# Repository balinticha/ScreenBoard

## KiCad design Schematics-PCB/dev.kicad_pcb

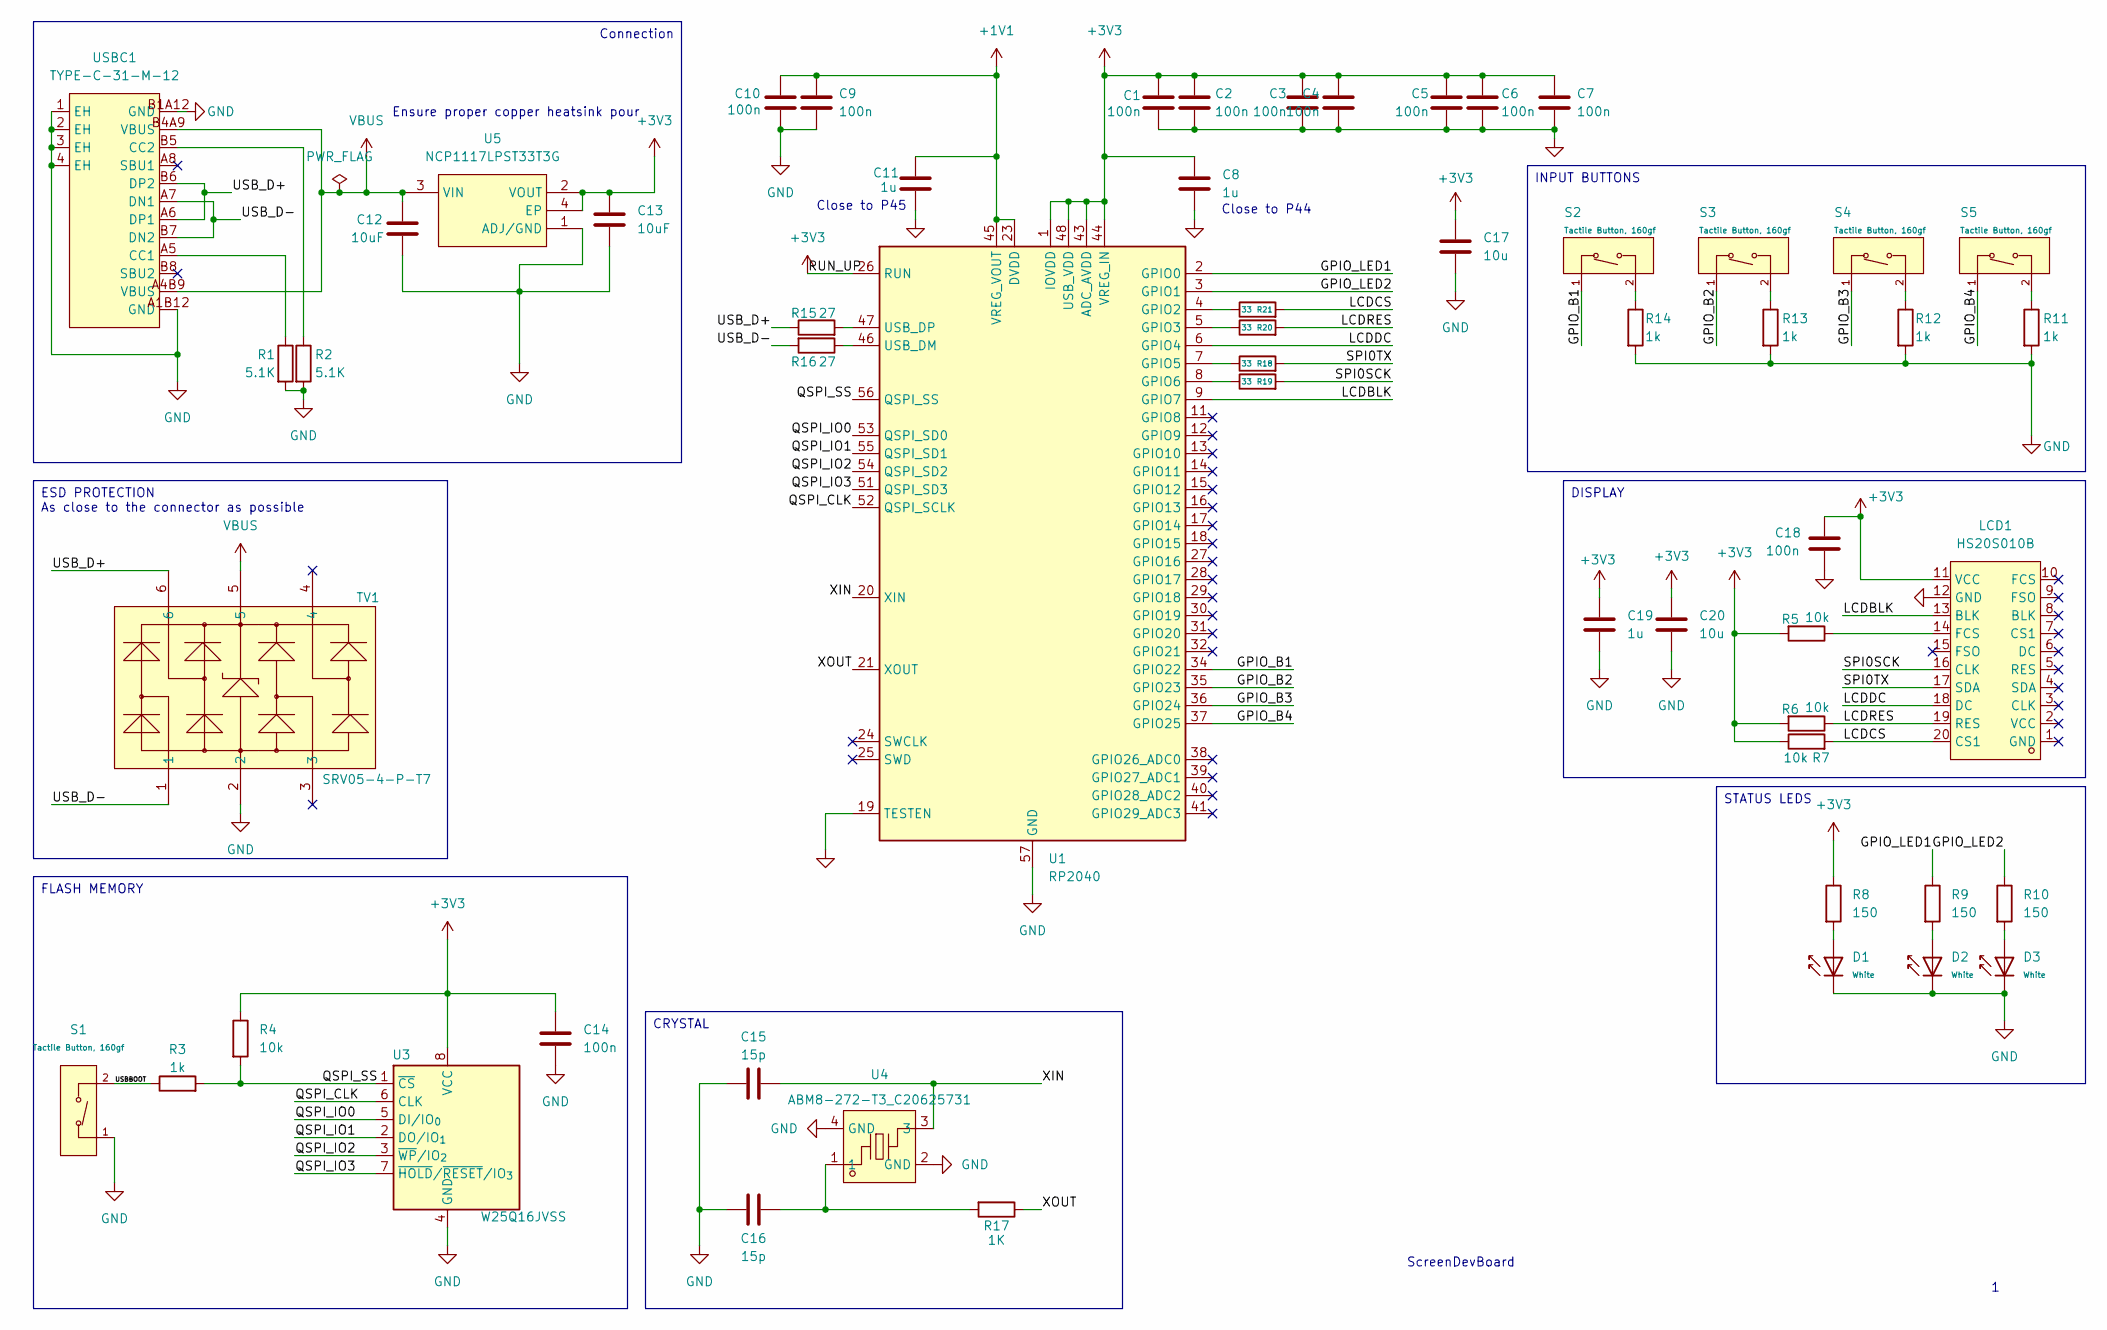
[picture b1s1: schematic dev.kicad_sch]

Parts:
C1, C2, C3, C4, C5, C6, C7, C9, C10: 100n; C_0402_1005Metric
C8, C11: 1u; C_0402_1005Metric
C12, C13: 10uF; C_0603_1608Metric
C14, C18: 100n; C_0603_1608Metric
C15, C16: 15p; C_0402_1005Metric
C17, C20: 10u; C_0603_1608Metric
C19: 1u; C_0603_1608Metric
D1, D2, D3: White; D_0805; Part KT-0805W; LCSC C34499
LCD1: HS20S010B; LCD-TH_HS20S010B; LCSC Part C5329586
R1, R2: 5.1K; R_0402_1005Metric
R3, R11, R12, R13, R14: 1k; R_0603_1608Metric
R4, R5, R6, R7: 10k; R_0603_1608Metric
R8, R9, R10: 150; R_0603_1608Metric
R15, R16: 27; R_0402_1005Metric
R17: 1K; R_0402_1005Metric
R18, R19, R20, R21: 33; R_0402_1005Metric
S1, S2, S3, S4, S5: Tactile Button, 160gf; SW_TS-1088-AR02016; Voltage Rating (Dc) 12V; Part TS-1088-AR02016; LCSC C720477
TV1: SRV05-4-P-T7; SOT-23-6_L2.9-W1.6-P0.95-LS2.8-BR; LCSC Part C85364
U1: RP2040; QFN-56-1EP_7x7mm_P0.4mm_EP3.2x3.2mm_ThermalVias; LCSC C2040
U3: W25Q16JVSS; SOIC-8_5.3x5.3mm_P1.27mm
U4: ABM8-272-T3_C20625731; CRYSTAL-SMD_4P-L3.2-W2.5-BL; LCSC Part C20625731
U5: NCP1117LPST33T3G; SOT-223_L6.5-W3.5-P2.30-LS7.0-BR; LCSC Part C146799
USBC1: TYPE-C-31-M-12; USB-C_SMD-TYPE-C-31-M-12_1; LCSC Part C165948

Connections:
+1V1: C9.1, C10.1, C11.1, U1.23 (DVDD), U1.45 (VREG_VOUT), U1.50 (DVDD)
+3V3: C1.1, C2.1, C3.1, C4.1, C5.1, C6.1, C7.1, C8.1, C13.1, C14.1, C17.1, C18.2, C19.1, C20.1, LCD1.11 (VCC), R4.1, R5.2, R6.2, R7.1, R8.1, U1.1 (IOVDD), U1.10 (IOVDD), U1.22 (IOVDD), U1.26 (RUN), U1.33 (IOVDD), U1.42 (IOVDD), U1.43 (ADC_AVDD), U1.44 (VREG_IN), U1.48 (USB_VDD), U1.49 (IOVDD), U3.8 (VCC), U5.2 (VOUT), U5.4 (EP)
/GPIO_B1: S2.1 (A), U1.34 (GPIO22)
/GPIO_B2: S3.1 (A), U1.35 (GPIO23)
/GPIO_B3: S4.1 (A), U1.36 (GPIO24)
/GPIO_B4: S5.1 (A), U1.37 (GPIO25)
/GPIO_LED1: R9.1, U1.2 (GPIO0)
/GPIO_LED2: R10.1, U1.3 (GPIO1)
/LCDBLK: LCD1.13 (BLK), U1.9 (GPIO7)
/LCDCS: LCD1.20 (CS1), R7.2, R21.2
/LCDDC: LCD1.18 (DC), U1.6 (GPIO4)
/LCDRES: LCD1.19 (RES), R6.1, R20.2
/QSPI_CLK: U1.52 (QSPI_SCLK), U3.6 (CLK)
/QSPI_IO0: U1.53 (QSPI_SD0), U3.5 (DI/IO_{0})
/QSPI_IO1: U1.55 (QSPI_SD1), U3.2 (DO/IO_{1})
/QSPI_IO2: U1.54 (QSPI_SD2), U3.3 (~WP/IO_{2})
/QSPI_IO3: U1.51 (QSPI_SD3), U3.7 (~HOLD/~RESET/IO_{3})
/QSPI_SS: R3.2, R4.2, U1.56 (QSPI_SS), U3.1 (~CS)
/SPI0SCK: LCD1.16 (CLK), R19.2
/SPI0TX: LCD1.17 (SDA), R18.2
/USBBOOT: R3.1, S1.2 (B)
/USB_D+: R15.1, TV1.6, USBC1.A6 (DP1), USBC1.B6 (DP2)
/USB_D-: R16.2, TV1.1, USBC1.A7 (DN1), USBC1.B7 (DN2)
/XIN: C15.2, U1.20 (XIN), U4.3
/XOUT: R17.1, U1.21 (XOUT)
GND: C1.2, C2.2, C3.2, C4.2, C5.2, C6.2, C7.2, C8.2, C9.2, C10.2, C11.2, C12.2, C13.2, C14.2, C15.1, C16.1, C17.2, C18.1, C19.2, C20.2, D1.1, D2.1, D3.1, LCD1.12 (GND), R1.2, R2.2, R11.2, R12.2, R13.2, R14.2, S1.1 (A), TV1.2, U1.19 (TESTEN), U1.57 (GND), U3.4 (GND), U4.2 (GND), U4.4 (GND), U5.1 (ADJ/GND), USBC1.1 (EH), USBC1.2 (EH), USBC1.3 (EH), USBC1.4 (EH), USBC1.A1B12 (GND), USBC1.B1A12 (GND)
unnamed: C16.2, R17.2, U4.1
unnamed: D1.2, R8.2
unnamed: D2.2, R9.2
unnamed: D3.2, R10.2
unnamed: LCD1.14 (FCS), R5.1
unnamed: R14.1, S2.2 (B)
unnamed: R13.1, S3.2 (B)
unnamed: R12.1, S4.2 (B)
unnamed: R11.1, S5.2 (B)
unnamed: R21.1, U1.4 (GPIO2)
unnamed: R20.1, U1.5 (GPIO3)
unnamed: R18.1, U1.7 (GPIO5)
unnamed: R19.1, U1.8 (GPIO6)
unnamed: R16.1, U1.46 (USB_DM)
unnamed: R15.2, U1.47 (USB_DP)
unnamed: R1.1, USBC1.A5 (CC1)
unnamed: R2.1, USBC1.B5 (CC2)
VBUS: C12.1, TV1.5, U5.3 (VIN), USBC1.A4B9 (VBUS), USBC1.B4A9 (VBUS)

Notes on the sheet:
Ensure proper copper heatsink pour
Close to P45
Close to P44
ScreenDevBoard
Connection
DISPLAY
STATUS LEDS
FLASH MEMORY
ESD PROTECTION As close to the connector as possible
INPUT BUTTONS
CRYSTAL

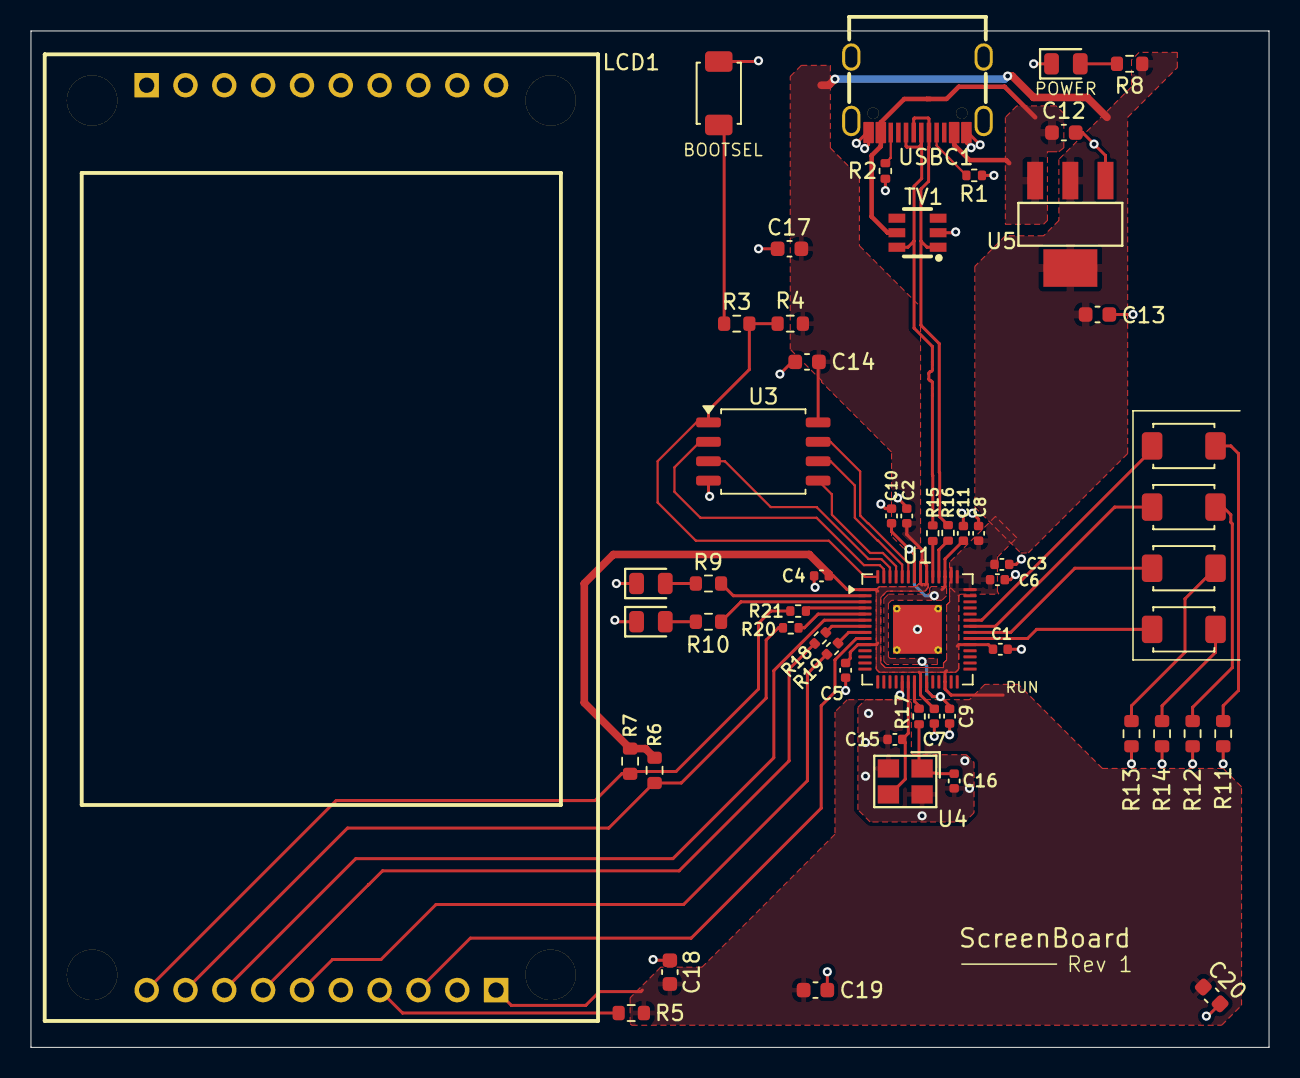
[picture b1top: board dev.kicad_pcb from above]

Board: 2 copper layers, 81.0 x 66.5 mm, 56 parts (0 on the bottom side), 44 nets.
